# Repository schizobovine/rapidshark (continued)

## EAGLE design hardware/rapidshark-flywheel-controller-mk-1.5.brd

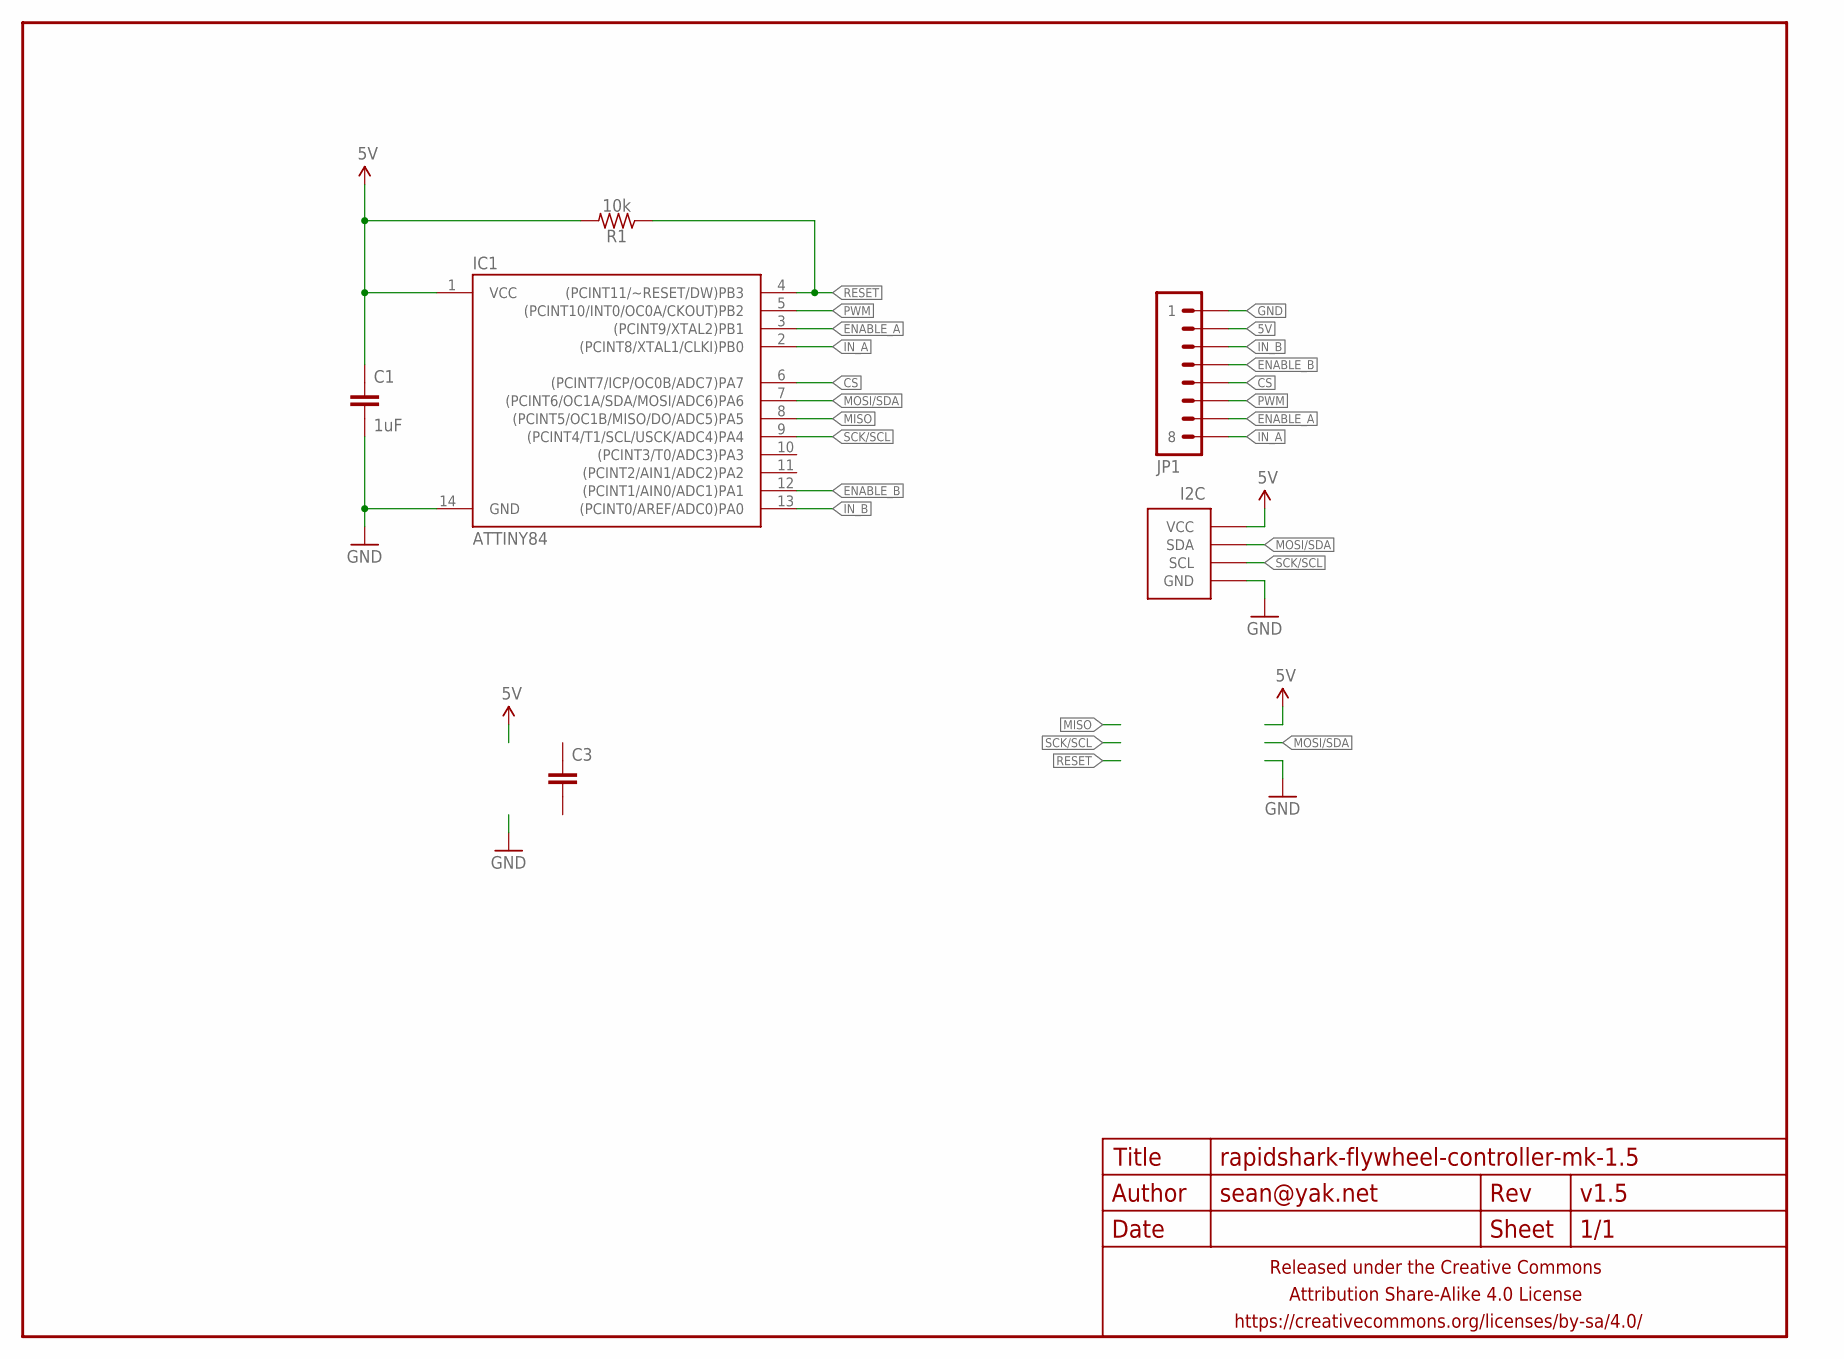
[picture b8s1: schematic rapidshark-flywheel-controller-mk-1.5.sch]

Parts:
C1: 1uF; C0603-TIGHTER
C3: CAPACITOR-CERAMICC0603-TIGHTER; C0603-TIGHTER
FRAME1: FRAME-LETTERNO_PACKAGE; DUMMY
I2C: M04-I2CJST-4-PH-RA-CENTERED; 1X04-JST-PH-RA-PTH-I2C-CENTERED
IC1: ATTINY84; SO14
JP1: M081X08; 1X08
R1: 10k; RESISTOR-AXIAL-PTH-5.08MM

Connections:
5V: C1.1, I2C.2 (VCC), IC1.1 (VCC), JP1.2, R1.P$2 (2)
CS: IC1.6 ((PCINT7/ICP/OC0B/ADC7)PA7), JP1.5
ENABLE_A: IC1.3 ((PCINT9/XTAL2)PB1), JP1.7
ENABLE_B: IC1.12 ((PCINT1/AIN0/ADC1)PA1), JP1.4
GND: C1.2, I2C.1 (GND), IC1.14 (GND), JP1.1
IN_A: IC1.2 ((PCINT8/XTAL1/CLKI)PB0), JP1.8
IN_B: IC1.13 ((PCINT0/AREF/ADC0)PA0), JP1.3
MISO: IC1.8 ((PCINT5/OC1B/MISO/DO/ADC5)PA5)
MOSI/SDA: I2C.3 (SDA), IC1.7 ((PCINT6/OC1A/SDA/MOSI/ADC6)PA6)
PWM: IC1.5 ((PCINT10/INT0/OC0A/CKOUT)PB2), JP1.6
RESET: IC1.4 ((PCINT11/~RESET/DW)PB3), R1.P$1 (1)
SCK/SCL: I2C.4 (SCL), IC1.9 ((PCINT4/T1/SCL/USCK/ADC4)PA4)

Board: 2 copper layers, 7 parts (1 on the bottom side), 11 nets, no tracks yet.

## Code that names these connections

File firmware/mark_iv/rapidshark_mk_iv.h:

/*
 * rapidshark_mk_iv.h
 *
 * Arduino microcontroller code to do All The Things to make darts fly. Various
 * defines, consts, enums and other programming wankery.
 *
 * Author: Sean "schizobovine" Caulfield <sean@yak.net>
 * License: GPLv2 (firmware) / CC4.0-BY-SA (documentation, hardware)
 *
 */

#ifndef __RAPIDSHARK_MK_IV_h
#define __RAPIDSHARK_MK_IV_h

////////////////////////////////////////////////////////////////////////
// CONSTANTS
////////////////////////////////////////////////////////////////////////

//
// Pin assignments
//


#define PIN_SW_PUSH     2
#define PIN_ACCEL_PWM   3
#define PIN_SW_CLIP     4
#define PIN_SW_ACCEL    5
#define PIN_SW_FIRE     6
#define PIN_PUSH_A      7
#define PIN_TACHOMETER  8
#define PIN_PUSH_B      9
#define PIN_PUSH_PWM    11
#define PIN_BUTT        13
#define PIN_DISP_RST    -1

//
// Display parameters
//

#define DISP_TEXT_SMALL 1
#define DISP_TEXT_LARGE 2
#define DISP_COLOR      WHITE
#define DISP_ADDR       0x3C
#define DISP_MODE       SSD1306_SWITCHCAPVCC

//
// Motor speed settings
//

#define MOTOR_ACCEL_SPEED     128
#define MOTOR_ACCEL_SPEED_MAX 255
#define MOTOR_PUSH_SPEED      96

// Number of microseconds per rotational period for 20krpm, the measured
// average speed at half-throttle, so we can full-throttle accelerate to that
// speed.
//
//                1
// tau = -------------------- * 1000 (ms/sec) * 1000 (us/ms)
//       20krpm / 60(sec/min)
//     = 60 * 1000 * 1000 / 20000 us
//     = 3000 us

#define MOTOR_ACCEL_SET_PERIOD (3000)

//
// Debounce intervals (in ms)
//

#define DEBOUNCE_TACHOMETER   (1)
#define DEBOUNCE_PUSH         (1)
#define DEBOUNCE_CLIP         (10)
#define DEBOUNCE_FIRE         (10)
#define DEBOUNCE_ACCEL        (10)
#define DEBOUNCE_BUTT         (10)

//
// Helper macros for readability
//
#define IS_PUSHER_EXTENDED  (switchPusher.read()==HIGH)
#define IS_PUSHER_RETRACTED (switchPusher.read()==LOW)
#define IS_ACC_TRIG_OPEN    (switchAccelTrigger.read()==HIGH)
#define IS_ACC_TRIG_CLOSED  (switchAccelTrigger.read()==LOW)
#define IS_FIRE_TRIG_OPEN   (switchFireTrigger.read()==HIGH)
#define IS_FIRE_TRIG_CLOSED (switchFireTrigger.read()==LOW)
#define IS_CLIP_INSERTED    (switchClipDetect.read()==HIGH)

////////////////////////////////////////////////////////////////////////
// PROTOTYPES
////////////////////////////////////////////////////////////////////////

bool finishedAccel();
void setMotorState();

void irq_tach_sens();
void irq_sw_push();
void irq_sw_clip();
void irq_sw_fire();
void irq_sw_accel();
void irq_butt_x();
void irq_butt_y();
void irq_butt_z();

void displayDecimal(uint8_t x, uint8_t y, int num);
void displayLabel(uint8_t x, uint8_t y, const char *text, bool invert);
void displayTextNormal();
void displayTextFlipped();
void displayRefresh();
void displayInit();
void displayDebugData();

void setup();
void loop();

#endif

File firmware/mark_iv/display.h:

/*
 * display.h
 *
 * Display code for the 128x64 OLED display.
 *
 * Author: Sean "schizobovine" Caulfield <sean@yak.net>
 * License: GPLv2 (firmware) / CC4.0-BY-SA (documentation, hardware)
 *
 */

#ifndef _DISPLAY_H
#define _DISPLAY_H

#include <stdlib.h>
#include <stdio.h>
#include <string.h>
#include <math.h>
#include <limits.h>
#include <avr/io.h>
#include <avr/pgmspace.h>
#include <avr/power.h>
#include <avr/sleep.h>

#include <Arduino.h>
#include <SPI.h>
#include <Wire.h>
#include <Adafruit_GFX.h>
#include <Adafruit_SSD1306.h>


class Display : public Adafruit_SSD1306 {
  public:
    Display(int8_t rst_pin);
    void refreshDisplay(
        uint8_t ammoCount,
        bool accelTrigger,
        bool fireTrigger,
        bool pusherLimit,
        bool dartDetector,
        bool clipDetector,
    );

  display.clearDisplay();

  displayTextNormal();
  display.setTextSize(4);
  display.setCursor(40, 0);
  display.print("37");

  display.setTextSize(1);

  displayLabel( 0, 40, "ACC" , (switchAccelTrigger.read()));
  displayLabel( 0, 48, "FIRE", (switchFireTrigger.read()));
  displayLabel( 0, 56, "PUSH", (switchPusher.read()));
  displayLabel(30, 40, "DART", (dartDetector.read()));
  displayLabel(30, 48, "CLIP", (switchClipDetect.read()));

  display.display();

}

void displayLabel(uint8_t x, uint8_t y, const char *text, bool invert) {
  display.setCursor(x, y);
  if (invert) {
    displayTextFlipped();
  } else {
    displayTextNormal();
  }
  display.print(text);
  displayTextNormal();
}

void displayTextNormal() {
  display.setTextColor(WHITE);
}

void displayTextFlipped() {
  display.setTextColor(BLACK, WHITE);
}
};

#endif

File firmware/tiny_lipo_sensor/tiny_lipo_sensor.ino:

/*
 * tiny_lipo_sensor.ino
 *
 * Fart out battery stats over some kind of serial.
 *
 */

#include <Arduino.h>

////////////////////////////////////////////////////////////////////////
// PIN ASSIGNMENT
////////////////////////////////////////////////////////////////////////

const uint8_t NUM_CELLS = 3;
const uint8_t CELL_PINS[NUM_CELLS] = {
  A0, // cell 1
  A1, // cell 2
  A2  // cell 3
};

const uint8_t EN_DIV  = 3; // PA3
const uint8_t PIN_CLK = 4; // PA4 aka SCLK aka SCL
const uint8_t PIN_DAT = 5; // PA5 aka MISO aka DO
const uint8_t PIN_EN  = 6; // PA6 aka MOSI aka DI aka SDA
const uint8_t LED = 8; // PA6 aka MOSI aka DI aka SDA

//
// Voltage divider calculations
//
//              R1 + R2
// Vin = Vout * -------
//                R2
//
// R1 = 4K7  (1%)
//    = 22K1 (1%)
//    = 36K  (1%)
// R2 = 10K  (1%, same for all)
//

////////////////////////////////////////////////////////////////////////
// GLOBAL STATE VARIABLES
////////////////////////////////////////////////////////////////////////

// Pre-calculated arrays of voltage divider multipliers, using some dirty fixed
// point math to avoid floating point. These times the 
const uint32_t VDIV[NUM_CELLS] = {
  5000L * ( 4900L + 10000L) / 10000L,
  5000L * (22100L + 10000L) / 10000L,
  5000L * (36000L + 10000L) / 10000L
};

// Number of bits of ADC resolution, used to divide reading after applying
// voltage divider multiplier (...which is a bit of an oxymoron now that I read
// it...).
const uint8_t ADC_NUM_BITS = 10;

// Readings in ADC ticks
volatile uint16_t readings_raw[NUM_CELLS] = {
  0, 0, 0
};

// Do ADC -> millivolt conversion with enough precision before dropping back to
// 16bit ints
volatile uint32_t reading_temp = 0;

// Readings in millivolts as 16-bit unsigned big-endian integers,
// double-buffered to allow us to serve results while computing the next set.
volatile uint16_t readings_buff[NUM_CELLS] = {
  0, 0, 0
};

// Size of the above buffer in BYTES
//const uint8_t BUFF_SZ = sizeof(uint16_t) * NUM_CELLS;
const uint8_t BUFF_SZ = 6;

// Buffer position
volatile uint8_t pos = 0;

// In SPI transaction
volatile boolean in_transaction = false;

// Max position in buffer by byte (not number), so we can transfer the MSB and
// LSB of the 16 bit results separately.
//const uint8_t BUFF_POS_MAX = NUM_CELLS * 2;

// Which of the two buffers is ready for reading by the master?
//volatile uint8_t curr_buff = 0;

// Where in that buffer the IRQ is reading from?
//volatile uint8_t buff_read_pos = BUFF_POS_MAX;

// Needed to prevent writer from swapping buffers while the other one is still
// being read in a SPI transaction.
//volatile boolean in_transaction = false;

// Software UARt for sharting data out
//SoftwareSerial serial(SERIAL_RX, SERIAL_TX);

////////////////////////////////////////////////////////////////////////
// HELPER FUNCTIONS
////////////////////////////////////////////////////////////////////////

// Do a full cylce of enabling voltage dividers & reading the ADC.
void do_read_voltages() {

  // Enable dividers by flipping Q4 (N-MOS) gate HIGH, thereby flipping the
  // gates for Q1, Q2 and Q3 (P-MOS) LOW, opening the connections to the cell
  // terminals.
  digitalWrite(EN_DIV, HIGH);

  // Wait a tick! The ADC needs time to stabilize.
  delay(10);

  // Do the needful
  readings_raw[0] = analogRead(CELL_PINS[0]);
  readings_raw[1] = analogRead(CELL_PINS[1]);
  readings_raw[2] = analogRead(CELL_PINS[2]);

  // Disable dividers by doing the reverse of the whole dance above. In
  // theory, you can take it back to tristate here, since the hardwired
  // "default" should be the safe/power-saving version that keeps all the
  // P-MOSFETs closed.
  digitalWrite(EN_DIV, LOW);

}

// Conversion from raw ADC values to millivolts. Written to a double-buffer to
// ensure consistent reads by the master.
void do_calc_voltages() {
  uint8_t i;

  // Figure out which buffer we need to write to, whichever is not the one
  // currently being read from. The switch between buffers is controlled by the
  // SPI transaction process, to ensure consistent reads.
  //other = (curr_buff + 1) % 2;

  // Calculate voltages
  for (i=0; i<NUM_CELLS; i++) {

    // Multiply by (R1+R2)/R1 * 1000
    //reading_temp = readings_raw[i] * VDIV[i];

    // Normalize by ADC precision & store
    //readings_buff[i] = reading_temp >> ADC_NUM_BITS;
    readings_buff[i] = readings_raw[i];

  }

}

// Busy wait based writing of buffers on bus. Helps that we can ignore the data
// from the master.
void put_buffers() {

  // Pre-put first byte
  USIDR = ((uint8_t*)readings_buff)[0];

  // Reset buff position
  pos = 1;

  // Put in transaction
  in_transaction = true;

  // Enable overflow interrupt
  USICR |= (1<<USIOIE);

  // Wait for transmission to finish
  while (in_transaction)
    ;

  // Disable overflow interrupt
  USICR &= ~(1<<USIOIE);


}

////////////////////////////////////////////////////////////////////////
// INTERRUPT HANDLERS
////////////////////////////////////////////////////////////////////////

// Interrupt handler for USI overflow vector, which gets called when slave
// transmission of a byte is complete. When this is tripped, we move the next
// byte into the transmission register and (optionally, we're not doing this)
// read out whatever the master sent us. Additionally, we advance buffer
// position, optionally swapping buffers if the other is ready.
ISR(USI_OVF_vect) {

  // Clear USI counter overflow
  USISR |= (1<<USIOIF);

  // If not in a transaction, what are we doing here?!?
  if (!in_transaction)
    return;

  // Put next byte on bus
  if (pos < BUFF_SZ) {
    USIDR = ((uint8_t*)readings_buff)[pos];
    pos += 1;
  }
  
  // If done with transaction, unblock main
  if (pos == BUFF_SZ) {
    in_transaction = false;
  }
  // Figure out which byte is next for reading
  //if (buff_read_pos < BUFF_MAX_POS) {

  // Transmission complete, set transaction flag off and repoint buffer at
  // start of array.
  //} else {
  //  buff_read_pos = 0;
  //  in_transaction = false;
  //}
}

////////////////////////////////////////////////////////////////////////
// STARTUP CODE
////////////////////////////////////////////////////////////////////////

void setup() {

  //delay(200);

  // Initialize divider to be default off
  pinMode(EN_DIV, OUTPUT);
  digitalWrite(EN_DIV, LOW);

  // Setup pins for "SPI" output
  pinMode(PIN_CLK, INPUT_PULLUP);
  pinMode(PIN_DAT, OUTPUT);
  pinMode(PIN_EN,  INPUT_PULLUP);

  pinMode(LED, OUTPUT);
  digitalWrite(LED, LOW);

  // Setup USI in 3-wire mode (though we'll be ignoring the input from the
  // master, since that's our enable line), with external clocking (slave mode)
  // on positive edges.
  USICR = (1<<USIWM0) | (1<<USICS1);

  readings_buff[0] = 1;
  readings_buff[1] = 2;
  readings_buff[2] = 3;

}

////////////////////////////////////////////////////////////////////////
// MAIN LOOP
////////////////////////////////////////////////////////////////////////

void loop() {

  // Check chip select pin to see if we should do jack and/or shit
  //if (digitalRead(PIN_EN) == LOW) {

    digitalWrite(LED, HIGH);
    do_read_voltages();
    do_calc_voltages();
    //readings_buff[0] += 3;
    //readings_buff[1] += 3;
    //readings_buff[2] += 3;
    put_buffers();
    digitalWrite(LED, LOW);

    // Voltage calculations
    //for (uint8_t i=0; i<NUM_CELLS; i++) {
    //  voltages[i] = calc_voltage(i);
    //}

    //
    // Fart out data
    //
    // Wire protocol is pretty basic: cell number followed by two bytes of data
    // (raw 10bit ADC value plus 6bits padding), with 0xFF signalling end of
    // data.
    //

    //serial.begin(SERIAL_BAUD);
    //serial.write((uint8_t)NUM_CELLS);
    //for (uint8_t i=0; i<NUM_CELLS; i++) {
    //  serial.write((uint8_t)(i+1)); // Cell num
    //  serial.write((uint8_t)((readings[i] >> 0) & 0xFF));
    //  serial.write((uint8_t)((readings[i] >> 8) & 0xFF));
    //}
    //serial.write((uint8_t)0xFF);
    //serial.flush();
    //serial.end();

    //// Because I'm feeling sassy. And hate battery life (despite desiging this
    //// whole circuit around it (don't judge my hypocracy! :P)).
    //delay(100);

  //}

}

// vi: syntax=arduino

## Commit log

2015-09-09 initial checkin of some rambling docs
2015-09-09 checkin of hardware files so far and firmware
2015-09-13 actually working version based on a rotary switch instead of mislabeled quadrature encoder
2015-10-02 changed to use a DIP switch because fuck it
2015-10-02 various new versions of the main connector board
2015-10-02 level shifter for the *@(^+ SparkFun OLED
2015-10-03 smaller connector board to squeeze past the big ass cap
2015-10-03 you know, i don't think i have enough revisions of this yet
2015-10-16 tweaks to jst part hole sizes
2015-10-16 various attempts to make a voltmeter to measure cell voltage in the battery
2015-10-16 attempting to make the sparkfun oled display 5V compatible and easier for i2c
2015-10-16 first attempt at documenting another oled board for purposes of getting laser cut parts for it
2015-10-16 anthoer button board
2015-10-16 actually bothered to layout this one
2015-10-16 relayout in metric
2015-10-18 layout for laser cutting
2015-10-18 removing duds
2015-10-18 removing/cleanup
2015-10-18 sed ftw
2015-10-18 more sed ftw
2015-10-18 final sed ftw
2015-10-18 whoops forgot to remove calibration sq from this one
2015-10-18 adjusting corner rounding
2015-10-18 changing to match the ABS one
2015-10-18 prettier colors
2015-10-18 exported AutoCAD DXF files
2015-10-18 renaming to something more meaningful
2015-10-22 relayout and now provides both 3V and 5V to display (but assumes IO voltage is whatever the arduino sends out
2015-10-22 attempt to build a display butt for sparkfun oled
2015-10-23 layout for sf butt adapter complete
2015-10-24 adding arduino makefile as submodule
2015-10-24 renaming nets so i can copypasta into the sketch
2015-10-24 libraries in case you don't like my butts convention (sorry-not-sorry)
2015-10-24 net/part/pinlists
2015-10-24 initial code skeleton
2015-10-28 adding adafruit libs as submodules
2015-10-28 making things compile/work for testing
2015-10-28 new board to add i2c pullups
2015-10-28 removing this board that's not gonna get made
2015-10-28 decrement version now
2015-10-28 renaming -fab files to their parents since that was dumb
2015-10-28 rename step 2
2015-10-28 removing some other dead boards
2015-10-28 use QSE-159 optoswitch for better noise immunity
2015-10-28 finishing resistor add layout
2015-10-28 simplified resistor add without reset or 3.3V to display
2015-11-03 adding EnableInterrupt library
2015-11-03 simple object to encapsulate motor control
2015-11-03 skeletonification and some testing code
2015-11-03 setting submodule to master
2015-11-03 resetting to master
2015-11-03 removing official lib and going with fork
2015-11-03 ugh changing upstream for submodules is annoying
2015-11-03 peg submodule to correct display size
2015-11-03 initial interrupt routine layout
2015-11-07 how i interrupt
2015-11-07 new version to tweak a few layout/silkscreen issues
2015-11-08 adding my fork of Bounce2
2015-11-08 sync to master
2015-11-08 adding bounce2 lib
2015-11-08 fixed silkscreen on 0602 resistor package
2015-11-10 rework to include sleeping, separate header file, motor object changes
2015-11-10 twiddling about with interrupts
2015-11-11 commit for beletion
2015-11-11 BELETED
2015-11-11 more state machine logic
2015-11-13 adding state to motor control class
2015-11-15 mostly complete state control added
2015-11-21 set motors and update display on every loop() call
2015-11-21 change to directly read debouncers. reduce user buttons to only one.
2015-11-21 debugging pusher
2015-11-22 breaking out fire mode control
2015-11-22 restoring sleep cycling
2015-11-22 mode switching
2015-11-22 Revert "breaking out fire mode control"
    This reverts commit fe47e61f974774da0fce26976c971ae77f6df7a7.
2015-11-22 Revert "Revert "breaking out fire mode control""
    This reverts commit 9375ccac8e7b97cbc899d3c130f71f3d9cef65df.
2015-11-22 Restoring multi-button code but keeping sleeping
    This reverts commit eb53e6b5dc9cd32bc981d69df92df141fb3282ce.
    Conflicts:
    firmware/mark_iv/rapidshark_mk_iv.ino
2015-11-22 restoring intertupts for buttons and other data structs
2015-11-22 cycle through fire control modes
2015-11-22 oiklasjifalsdkfjdwsaf
2015-11-22 i hate c++, but ammo counter now broken out
2015-11-22 almost done except for infinite pusher loop
2015-11-22 new backlight board for dart detection
2015-11-22 tweaking debounce time interval
2015-11-22 works! fixed bug where pusher wasn't fully retracting due to pwm cycle not being high enough to fully brake motor
2015-11-22 removing test_safe code
2015-11-22 cleaning up unused code
2015-11-23 gotta go fast
2015-11-23 more speedup code
2015-11-23 dakfladsjlfjlasfjsd
2015-11-23 pausing b/c i need a break, but pwm on accel is fucked
2015-11-25 tachometer stub module
2015-11-25 breaking out display functions
2015-11-25 removing display code after breaking out; capitalize constants
2015-11-25 removing accel code from here; will place closed loop control in another module
2015-11-26 more tach mods
2015-11-26 welp
2015-11-28 more debugging rpm sensing
2015-11-28 think i got this but readings are very volatile so need more smoothing
2015-11-28 first pass at closed loop flywheel control
2015-11-29 herp derp inverted period and freq; disabling tach results until buffer full
2015-11-29 adding max rpm display between runs
2015-11-29 apparently it still just refuses to display anything but zero
2015-12-08 some testing code for measuring battery voltage
2015-12-08 don't need vfprintf bloating code
2015-12-08 lipo voltage testing boards
2015-12-08 attempts at my own very special and not good h bridge
2015-12-08 first try at removal
2015-12-08 adding with compile-able name
2015-12-08 some more compilation fixes
2016-02-02 battery level firmware test
2016-02-02 unfinished hardware design for a battery level tester which reports over SPI/I2c
2016-02-02 unfinished new revision of OLED backpack for sparkfun's microview breakout after a single attempt at building one
2016-02-02 a number of smaller discrete mosfet partial bridges to hit accceleration target
2016-03-23 silkscreen changes
2016-04-16 feather based display idea, lipo charger disaster
2016-04-16 adding these to commit to log before shifting to another repo
2016-04-16 removing now in uvdosimeter repo where they belong
2016-08-07 testing wip
2016-08-17 motor butt plate to make less EM farts
2016-08-17 discrete half bridge with optoisolated gate drivers
2016-08-17 half bridge using A3946 controller
2016-08-19 WIP A3946 half bridge driver
2016-08-20 wip full bridge
2016-08-20 simpler half bride wip
2016-09-07 more twiddling around with cheap h-bridge ideas
2016-09-07 yet more twiddling around with cheap h-bridge ideas
2016-09-07 first pass BLDC ESC, this should end well
2016-10-01 more bridge shenanigans
2016-10-01 battery sensor
2016-10-01 motor driver fault displayer plus connector dongle
2016-10-02 fix revision on silkscreen/board
2016-10-02 new revision for some driver changes
2016-10-10 asdlkfjaklsdfjsdlk
2016-10-10 MOAR BREAKOUTZ
2016-10-10 documentationes
2016-10-10 new motor testing rig with rotary encoder
2016-10-11 oops need lib
2016-10-11 motor TESTIFY
2016-10-11 adding sensor for lipo battery
2016-10-11 adding for deletion
2016-10-11 first attempt at lipo sensor firmware
2016-10-12 slightly revised sensor protocol
2016-10-12 arduino library to communicate with sensor
2016-10-21 WIP lipo sensor
2016-10-22 screw it SPI go
2016-10-29 look i change my mind a lot ok
2017-01-22 lipo sensor stuff
2017-01-22 apparently i started on yet more revisions???
2017-02-14 futzing with firmware
2017-02-14 examples used for usi
2017-02-14 lipo sensors suck
2017-02-14 new connector board for new motor driver and lipo sensor
2017-02-14 maybe i was going to use this?
2017-02-14 teensy version maybe someday
2017-10-05 oh hey more hardware fails
2017-10-05 firmware updates wip
2017-12-14 lipo sensor test program
2017-12-14 new teensy lc mainboard with vreg
2017-12-14 updates due to new hardware tweaks
2017-12-14 further attempts at firmware rewrites
2018-09-30 wip?
